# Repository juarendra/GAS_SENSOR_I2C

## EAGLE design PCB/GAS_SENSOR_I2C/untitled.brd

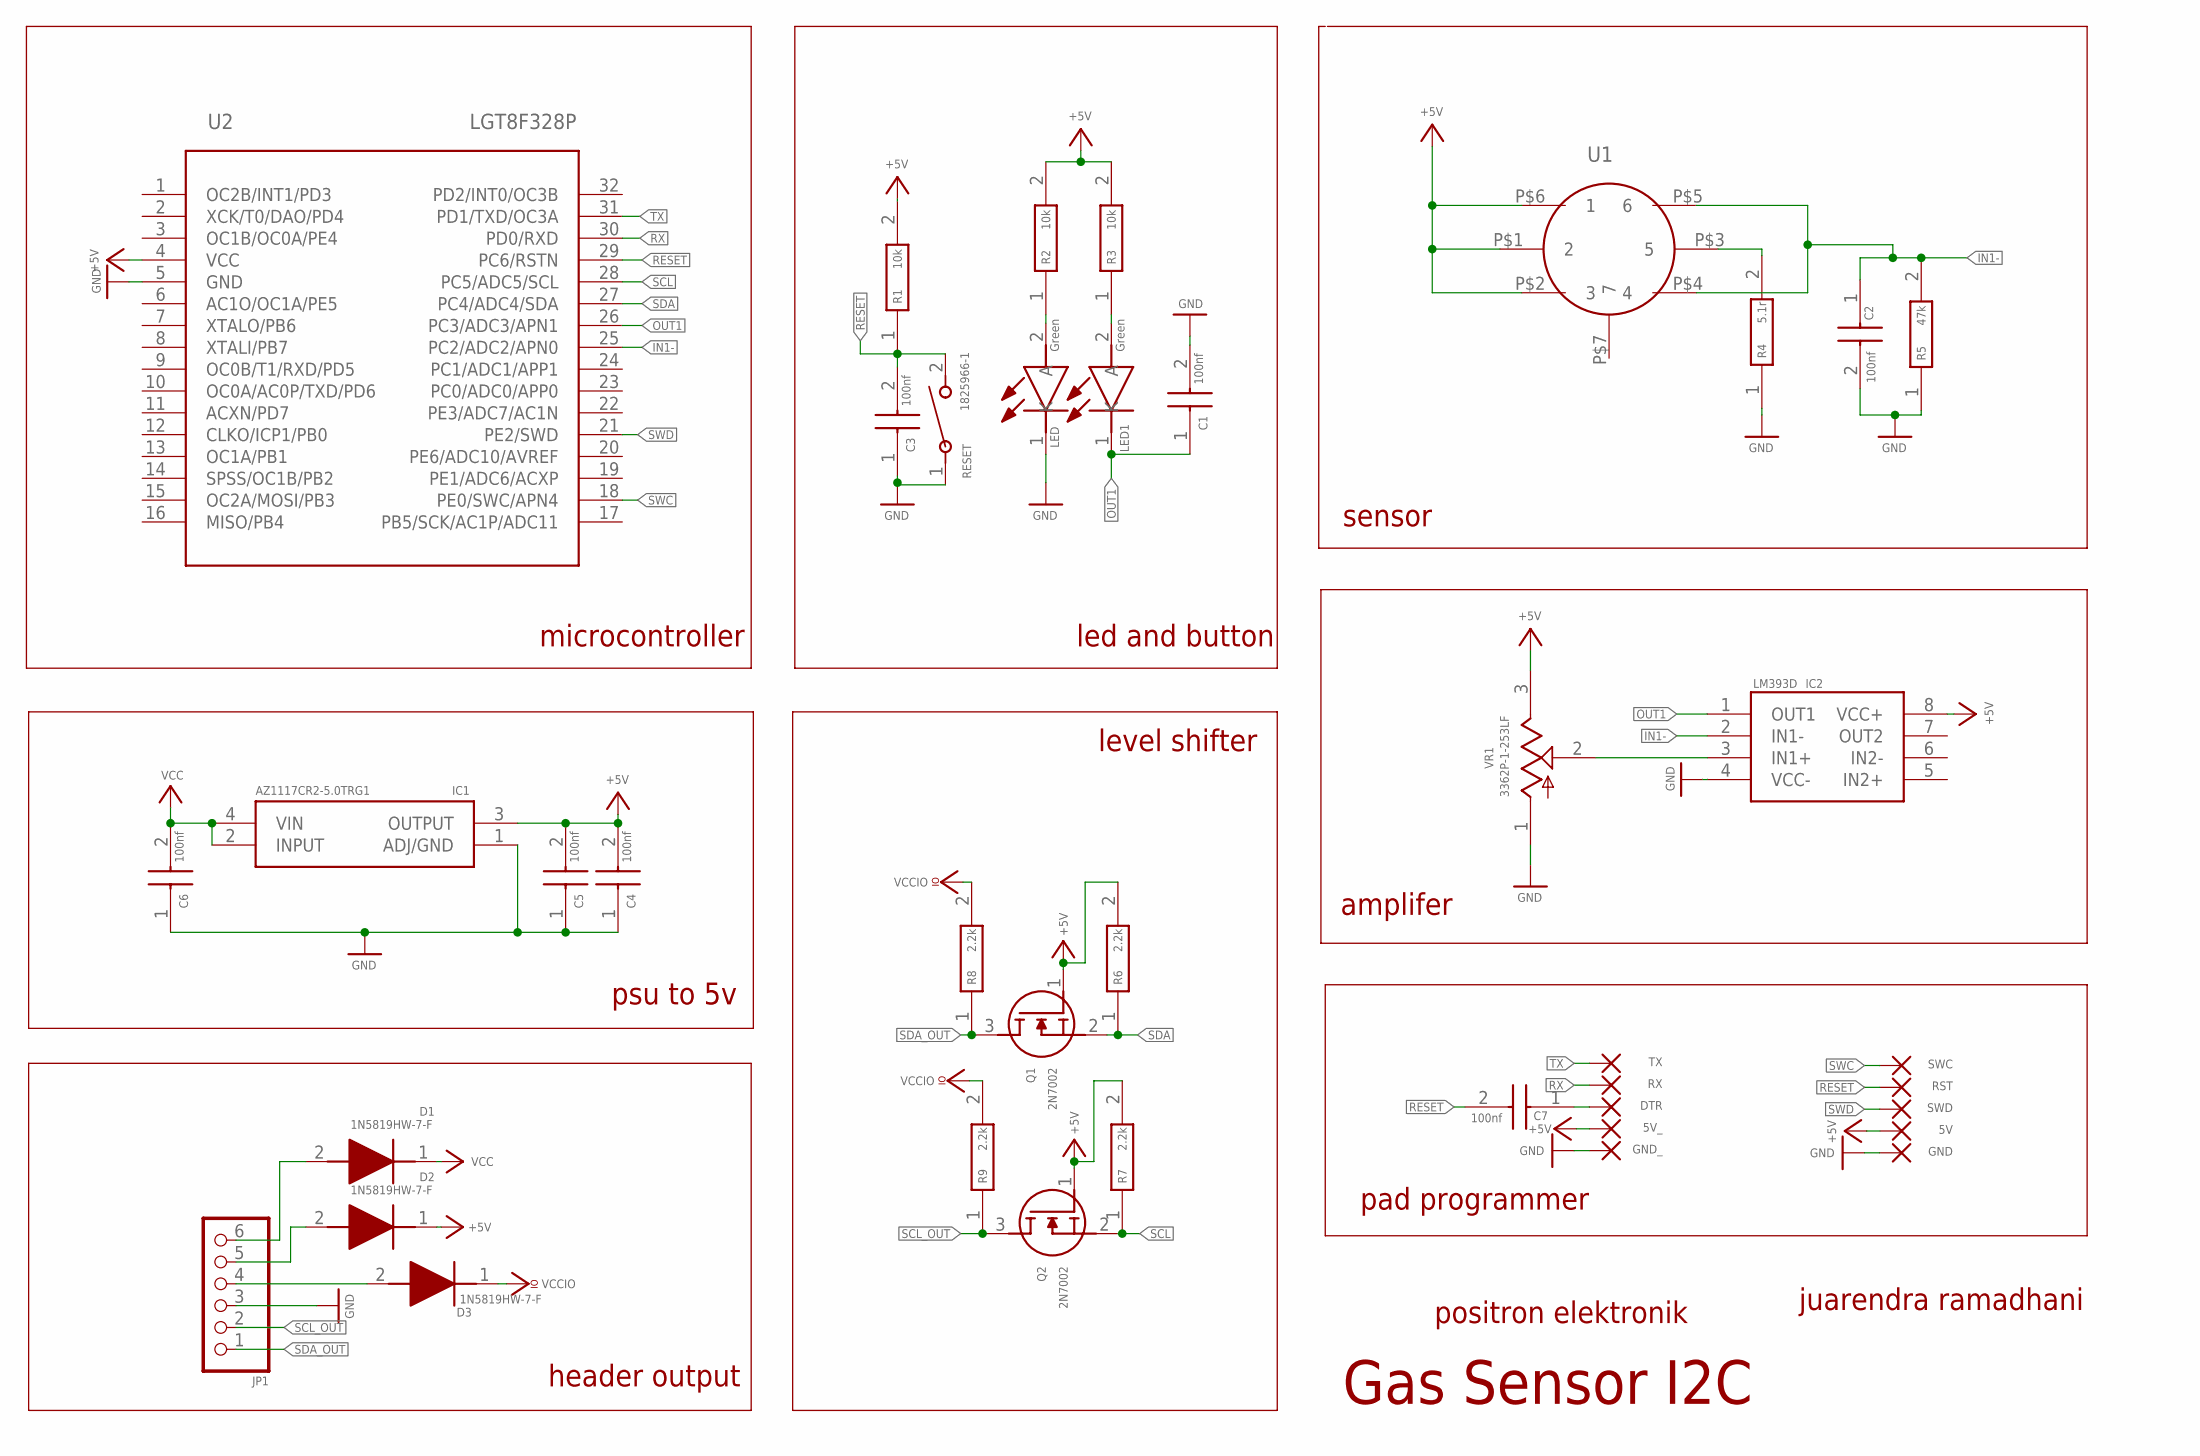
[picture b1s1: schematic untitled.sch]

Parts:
5V, 5V_: SMD2; SMD1,27-2,54
C1, C2, C3, C4, C5, C6, C7: 100nf; CAPC1608X90N
D1, D2, D3: 1N5819HW-7-F; SOD3716X145N
DTR: SMD2; SMD1,27-2,54
GND: SMD2; SMD1,27-2,54
GND_: SMD2; SMD1,27-2,54
IC1: AZ1117CR2-5.0TRG1; AP738133Y13
IC2: LM393D; SOIC127P600X175-8N
JP1: PINHD-1X6; 1X06
LED, LED1: Green; LEDC2012X80N
Q1, Q2: 2N7002; SOT95P280X125-3N
R1, R2, R3: 10k; RESC1608X50N
R4: 5.1r; RESC1608X55N
R5: 47k; RESC1608X55N
R6, R7, R8, R9: 2.2k; RESC1608X55N
RESET: 1825966-1; SWDIP2_256X170P100
RST: SMD2; SMD1,27-2,54
RX: SMD2; SMD1,27-2,54
SWC: SMD2; SMD1,27-2,54
SWD: SMD2; SMD1,27-2,54
TX: SMD2; SMD1,27-2,54
U1: MQ-SOCKET; TQFP32-08
U2: LGT8F328P; TQFP32-08
VR1: 3362P-1-253LF; TRIM_3362P-1-253LF

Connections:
+5V: 5V.1, 5V_.1, C4.2, C5.2, D2.1 (K), IC1.3 (OUTPUT), IC2.8 (VCC+), Q1.1 (G), Q2.1 (G), R1.2, R2.2, R3.2, R6.2, R7.2, U1.P$1 (2), U1.P$2 (3), U1.P$6 (1), U2.4 (VCC), VR1.3 (CW)
GND: C1.2, C2.2, C3.1, C4.1, C5.1, C6.1, GND.1, GND_.1, IC1.1 (ADJ/GND), IC2.4 (VCC-), JP1.3, LED.1 (K), R4.1, R5.1, RESET.1, U2.5 (GND), VR1.1 (CCW)
IN1-: C2.1, IC2.2 (IN1-), R5.2, U1.P$4 (4), U1.P$5 (6), U2.25 (PC2/ADC2/APN0)
unnamed: LED.2 (A), R2.1
unnamed: LED1.2 (A), R3.1
unnamed: R4.2, U1.P$3 (5)
unnamed: D1.2 (A), JP1.6
unnamed: D3.2 (A), JP1.4
unnamed: IC2.3 (IN1+), VR1.2 (WIPER)
unnamed: D2.2 (A), JP1.5
unnamed: C7.1, DTR.1
OUT1: C1.1, IC2.1 (OUT1), LED1.1 (K), U2.26 (PC3/ADC3/APN1)
RESET: C3.2, C7.2, R1.1, RESET.2, RST.1, U2.29 (PC6/RSTN)
RX: RX.1, U2.30 (PD0/RXD)
SCL: Q2.2 (S), R7.1, U2.28 (PC5/ADC5/SCL)
SCL_OUT: JP1.2, Q2.3 (D), R9.1
SDA: Q1.2 (S), R6.1, U2.27 (PC4/ADC4/SDA)
SDA_OUT: JP1.1, Q1.3 (D), R8.1
SWC: SWC.1, U2.18 (PE0/SWC/APN4)
SWD: SWD.1, U2.21 (PE2/SWD)
TX: TX.1, U2.31 (PD1/TXD/OC3A)
VCC: C6.2, D1.1 (K), IC1.2 (INPUT), IC1.4 (VIN)
VCCIO: D3.1 (K), R8.2, R9.2

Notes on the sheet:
positron elektronik
juarendra ramadhani
Gas Sensor I2C
level shifter
led and button
sensor
amplifer
pad programmer
header output
psu to 5v
microcontroller

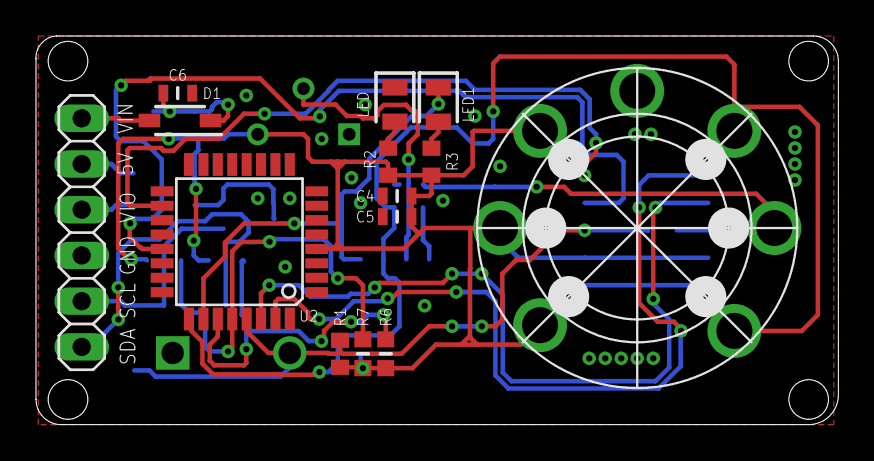
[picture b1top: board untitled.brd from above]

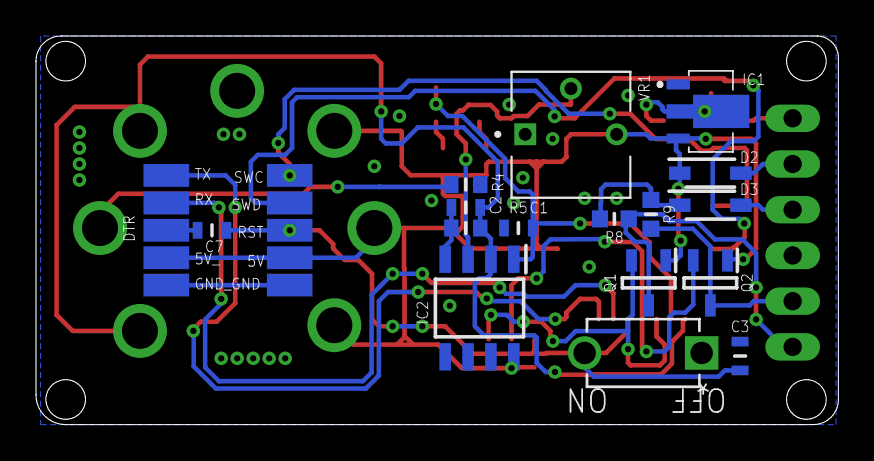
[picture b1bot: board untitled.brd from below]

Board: 2 copper layers, 44.6 x 21.6 mm, 40 parts (26 on the bottom side), 23 nets.

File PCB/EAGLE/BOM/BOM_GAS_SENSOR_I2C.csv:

"Qty";"Value";"Device";"Package";"Parts";"Description";"AVAILABILITY";"BUILT_BY";"CATEGORY";"CHECK_PRICES";"COPYRIGHT";"DESCRIPTION";"HEIGHT";"MANUFACTURER_NAME";"MANUFACTURER_PART_NUMBER";"MF";"MOUSER_PART_NUMBER";"MOUSER_PRICE-STOCK";"MP";"PACKAGE";"PART_STATUS";"POPULARITY";"PRICE";"SERIES";"SNAPEDA_LINK";"VALUE";"VENDOR";
"1";"";"MQ-SOCKET";"TQFP32-08";"U1";"Check availability";"";"";"";"";"";"";"";"";"";"";"";"";"";"";"";"";"";"";"";"";"";
"1";"";"PINHD-1X6";"1X06";"JP1";"PIN HEADER";"";"";"";"";"";"";"";"";"";"";"";"";"";"";"";"79";"";"";"";"";"";
"10";"";"SMD2";"SMD1,27-2,54";"5V, 5V_, DTR, GND, GND_, RST, RX, SWC, SWD, TX";"SMD PAD";"";"";"";"";"";"";"";"";"";"";"";"";"";"";"";"15";"";"";"";"";"";
"7";"100nf";"CGA3E3X7S2A104M080AB";"CAPC1608X90N";"C1, C2, C3, C4, C5, C6, C7";"Multilayer Ceramic Chip Capacitors, Capacitance=0.1uF, LxWxT:1.6x0.8x0.8mm";"";"";"";"";"";"Multilayer Ceramic Chip Capacitors, Capacitance=0.1uF, LxWxT:1.6x0.8x0.8mm";"0.9mm";"TDK";"CGA3E3X7S2A104M080AB";"";"810-CGA3E3X7S2A104AB";"https://www.mouser.co.uk/ProductDetail/TDK/CGA3E3X7S2A104M08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";"";"";"";"";"";"";"";"";"";
"3";"10k";"CRCW060310K0FKEI";"RESC1608X50N";"R1, R2, R3";"Standard Thick Film Chip Resistors value 10K0 ohm.";"";"";"";"";"";"Standard Thick Film Chip Resistors value 10K0 ohm.";"0.5mm";"Vishay";"CRCW060310K0FKEI";"";"71-CRCW060310K0FKEI";"https://www.mouser.co.uk/ProductDetail/Vishay-Dale/CRCW06031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";"";"";"";"";"";"";"";"";"";
"1";"1825966-1";"1825966-1";"SWDIP2_256X170P100";"RESET";"";"";"EMA_UL_Team";"Tactile Switches";"";"Copyright (C) 2016 Accelerated Designs. All rights reserved";"FSMCH=3.5 X 6.0 X 4.3 TACT SWITCH, HT";"";"";"1825966-1";"";"";"";"";"";"active";"";"";"Unknown";"";"";"TE Connectivity";
"3";"1N5819HW-7-F";"1N5819HW-7-F";"SOD3716X145N";"D1, D2, D3";"Diode Schottky 1A 40V SOD123 Diodes Inc 1N5819HW-7-F, SMT Schottky Diode, 40V 1A, 2-Pin SOD-123";"";"";"";"";"";"Diode Schottky 1A 40V SOD123 Diodes Inc 1N5819HW-7-F, SMT Schottky Diode, 40V 1A, 2-Pin SOD-123";"1.45mm";"Diodes Incorporated";"1N5819HW-7-F";"";"621-1N5819HW-F";"https://www.mouser.co.uk/ProductDetail/Diodes-Incorporated/1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";"";"";"";"";"";"";"";"";"";
"4";"2.2k";"CR0603-FX-2201ELF";"RESC1608X55N";"R6, R7, R8, R9";"BOURNS - CR0603-FX-2201ELF - RES, THICK FILM, 2K2, 1%, 0.1W, 0603";"";"";"";"";"";"BOURNS - CR0603-FX-2201ELF - RES, THICK FILM, 2K2, 1%, 0.1W, 0603";"0.55mm";"Bourns";"CR0603-FX-2201ELF";"";"652-CR0603FX-2201ELF";"https://www.mouser.co.uk/ProductDetail/Bourns/CR0603-FX-2201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";"";"";"";"";"";"";"";"";"";
"2";"2N7002";"2N7002";"SOT95P280X125-3N";"Q1, Q2";"This Power MOSFET is the second generation of STMicroelectronics unique single feature size strip-based process. The resulting transistor shows extremely high packing density for low onresistance, rugged avalanche characteristics and less critical alignment steps therefore a remarkable manufacturing reproducibility.";"";"";"";"";"";"This Power MOSFET is the second generation of STMicroelectronics unique single feature size strip-based process. The resulting transistor shows extremely high packing density for low onresistance, rugged avalanche characteristics and less critical alignment steps therefore a remarkable manufacturing reproducibility.";"1.25mm";"STMicroelectronics";"2N7002";"";"511-2N7002";"https://www.mouser.co.uk/ProductDetail/STMicroelectronics/2N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";"";"";"";"";"";"";"";"";"";
"1";"3362P-1-253LF";"3362P-1-253LF";"TRIM_3362P-1-253LF";"VR1";"Check availability";"In Stock";"";"";"https://www.snapeda.com/parts/3362P-1-253LF/Bourns/view-part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";"";"                                                      1/4 Sq, Thru-Hole, TRIMMER, 25 Kilohms, Cermet, Single Turn | Bourns 3362P-1-253LF                                              ";"";"";"";"Bourns";"";"";"3362P-1-253LF";"3362P-1 Bourns Inc.";"";"";"None";"";"https://www.snapeda.com/parts/3362P-1-253LF/Bourns/view-part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";"";"";
"1";"47k";"AC0603FR-7W47KL";"RESC1608X55N";"R5";"AEC-Q200 qualified  Moisture sensitivity level: MSL 1  AC series soldering is compliant with J-STD-020D  Halogen free epoxy";"";"";"";"";"";"AEC-Q200 qualified  Moisture sensitivity level: MSL 1  AC series soldering is compliant with J-STD-020D  Halogen free epoxy";"0.55mm";"YAGEO";"AC0603FR-7W47KL";"";"";"";"";"";"";"";"";"";"";"";"";
"1";"5.1r";"RT0603DRE075R1L";"RESC1608X55N";"R4";"Thin Film Resistors - SMD 1/10W 5.1 ohm .5% 50ppm";"";"";"";"";"";"Thin Film Resistors - SMD 1/10W 5.1 ohm .5% 50ppm";"0.55mm";"YAGEO";"RT0603DRE075R1L";"";"";"";"";"";"";"";"";"";"";"";"";
"1";"AZ1117CR2-5.0TRG1";"AZ1117CR2-5.0TRG1";"AP738133Y13";"IC1";"Linear Voltage Regulator IC Positive Fixed 1 Output 1A SOT-89-3";"";"";"";"";"";"Linear Voltage Regulator IC Positive Fixed 1 Output 1A SOT-89-3";"1.6mm";"Diodes Incorporated";"AZ1117CR2-5.0TRG1";"";"621-AZ1117CR25.0TRG1";"https://www.mouser.co.uk/ProductDetail/Diodes-Incorporated/A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";"";"";"";"";"";"";"";"";"";
"2";"Green";"150080BS75000";"LEDC2012X80N";"LED, LED1";"LED,Wurth Elektronik,150080BS75000 Wurth Elektronik 150080BS75000, WL-SMCW Series Blue LED, 470 nm 2012 (0805) Clear, Rectangle Lens SMD package";"";"";"";"";"";"LED,Wurth Elektronik,150080BS75000 Wurth Elektronik 150080BS75000, WL-SMCW Series Blue LED, 470 nm 2012 (0805) Clear, Rectangle Lens SMD package";"0.8mm";"Wurth Elektronik";"150080BS75000";"";"710-150080BS75000";"https://www.mouser.co.uk/ProductDetail/Wurth-Elektronik/1500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";"";"";"";"";"";"";"";"Green";"";
"1";"LGT8F328P";"LGT8F328P";"TQFP32-08";"U2";"Check availability";"Not in stock";"";"";"https://www.snapeda.com/parts/LGT8F328P/Arduino/view-part/?ref=eda";"";"                                                                                                    ";"";"";"";"Arduino";"";"";"LGT8F328P";"Package ";"";"";"None";"";"https://www.snapeda.com/parts/LGT8F328P/Arduino/view-part/?ref=snap";"";"";
"1";"LM393D";"LM393D";"SOIC127P600X175-8N";"IC2";"LM393D, Dual Comparator Open Collector 1.3us 12 V, 15 V, 18 V, 24 V, 28 V, 3 V, 5 V, 9 V 8-Pin SO";"";"";"";"";"";"LM393D, Dual Comparator Open Collector 1.3us 12 V, 15 V, 18 V, 24 V, 28 V, 3 V, 5 V, 9 V 8-Pin SO";"1.75mm";"STMicroelectronics";"LM393D";"";"511-LM393D";"https://www.mouser.co.uk/ProductDetail/STMicroelectronics/LM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";"";"";"";"";"";"";"";"";"";

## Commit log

2025-02-16 FEAT: update mq socket footprint
2025-02-19 FEAT: add image and 3d model
2025-02-19 FEAT: add readme

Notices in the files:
parts and their libraries:
COPYRIGHT: Copyright (C) 2016 Accelerated Designs. All rights reserved
